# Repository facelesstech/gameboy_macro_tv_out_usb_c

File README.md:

# gameboy_macro_tv_out_usb_c
gameboy_macro_tv_out_usb_c

  * [Blog post](https://facelesstech.wordpress.com/2024/04/27/gameboy-macro-tv-out-via-usb-c/)

  * [Youtube link](https://youtu.be/vSM3D0GghRg)

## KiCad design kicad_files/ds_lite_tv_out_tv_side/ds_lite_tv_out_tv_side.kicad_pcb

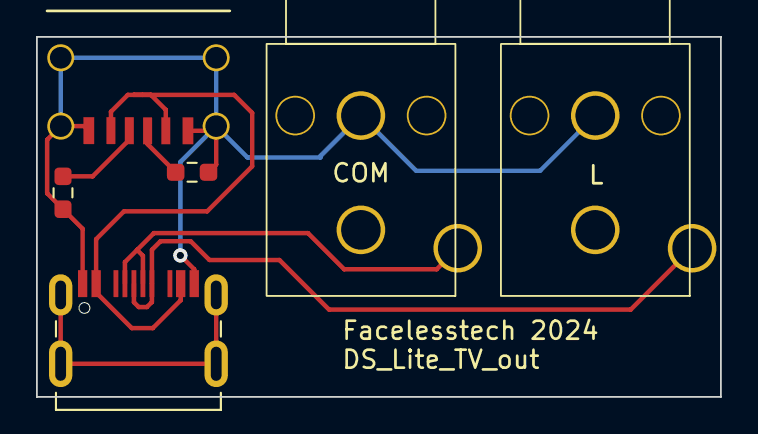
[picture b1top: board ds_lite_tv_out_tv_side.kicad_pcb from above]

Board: 2 copper layers, 38.0 x 20.0 mm, 6 parts (0 on the bottom side), 6 nets.

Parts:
J1, J2: Conn_Coaxial; RCA_female
P1: USB_C_Plug; USB_C_SMD_USB2
R1, R2: R; R_0603_1608Metric_Pad0.98x0.95mm_HandSolder
U1: usb_c_6pin; USB_C_6PIN_custom

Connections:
unnamed: J1.2 (Ext), J2.2 (Ext), P1.A1 (GND), P1.A12 (GND), R1.1, R2.1, U1.1 (GND)
unnamed: J1.1 (In), P1.A7 (D-)
unnamed: J2.1 (In), P1.A6 (D+)
unnamed: R2.2, U1.4 (CC1)
unnamed: R1.2, U1.3 (CC2)
unnamed: P1.A4 (VBUS), P1.A9 (VBUS), U1.2 (VBUS)

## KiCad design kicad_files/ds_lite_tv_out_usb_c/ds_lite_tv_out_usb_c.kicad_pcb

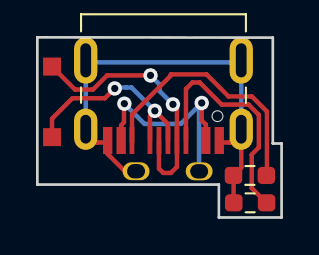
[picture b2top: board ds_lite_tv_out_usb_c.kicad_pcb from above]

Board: 2 copper layers, 13.6 x 10.0 mm, 6 parts (0 on the bottom side), 6 nets.

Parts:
BT1: Battery; ds_lite_charger_pins
Com: TestPoint; 1mm_test_point_square_SMD
L: TestPoint; 1mm_test_point_square_SMD
P1: USB_C_Plug; USB_C_SMD_USB2
R1, R2: R; R_0603_1608Metric_Pad0.98x0.95mm_HandSolder

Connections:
unnamed: BT1.1 (+), P1.A1 (GND), P1.A12 (GND), P1.S1 (SHIELD), R1.2, R2.2
unnamed: BT1.2 (-), P1.A4 (VBUS), P1.A9 (VBUS)
unnamed: P1.A5 (CC), R1.1
unnamed: L.1, P1.A6 (D+)
unnamed: Com.1, P1.A7 (D-)
unnamed: P1.B5 (VCONN), R2.1

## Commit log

2024-04-20 added license
2024-04-20 added PCB files
2024-04-20 added 3d print files
2024-04-27 added photo
2024-04-27 added photo and blog post link to readme
2024-04-27 spelling mistake
2024-04-27 added youtube link
